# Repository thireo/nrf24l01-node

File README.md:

Indoor climate measuring nodes running on a single coin cell battery. Measurements done every 5 minutes (not necessarily sent at same interval).

Specs. for now:

* NRF24L01 - 2.4GHz module
* SAMD21G18 - MCU
* CR2450 - Coin cell battery ~ 500+mAh
* BME280 - Temperature, Humidity & Pressure.
* DS1302 - Ultra low power RTC for waking up node / Perhaps instead TLP5010.

Ideas to improve battery life:
Latch/flippydifloppy to control power to MCU + SIP32431.

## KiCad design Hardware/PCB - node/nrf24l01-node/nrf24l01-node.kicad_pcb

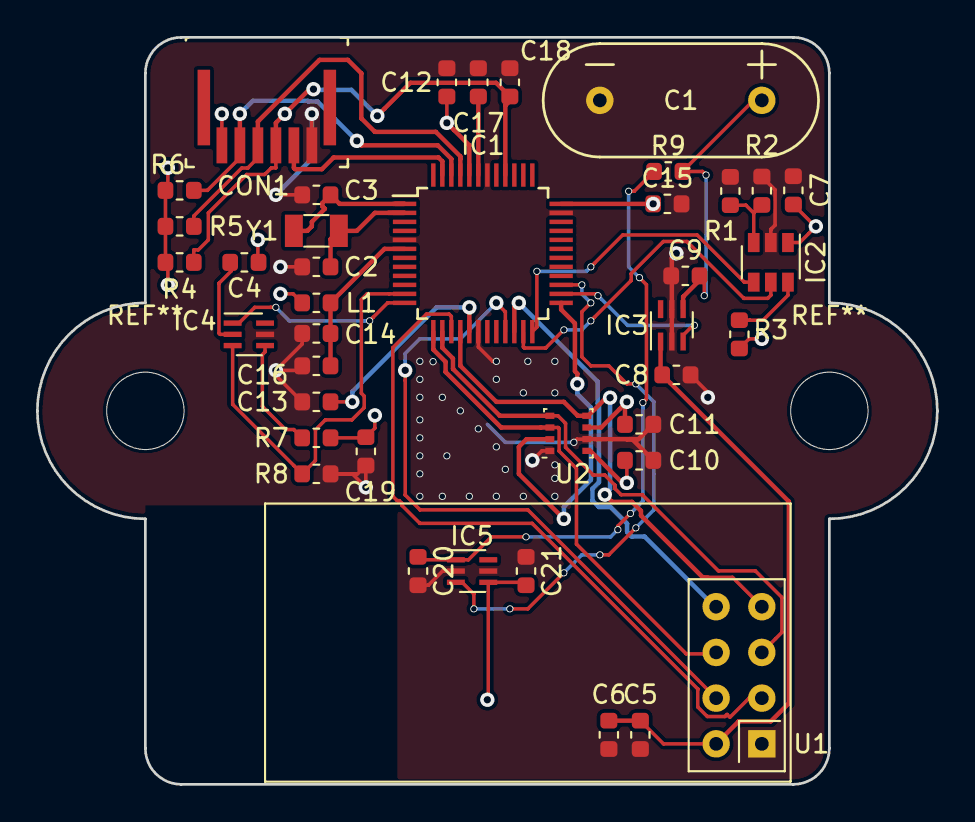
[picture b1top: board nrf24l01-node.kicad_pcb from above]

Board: 2 copper layers, 50.0 x 41.5 mm, 41 parts (1 on the bottom side), 30 nets.

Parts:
BT1: Coin Cell; BatteryHolder_Keystone_3008_1x2450
C1: SuperCap; SCMQ14C474PRBA0
C2, C3: 15pF; C_0603_1608Metric
C4, C6, C7, C8, C9, C10, C11, C13, C15, C16, C17, C18, C19, C20, C21: 100nF; C_0603_1608Metric
C5: 100uF; C_0603_1608Metric
C12, C14: 10uF; C_0603_1608Metric
CON1: FPC_6POS; HFW6R_2STE1LF
IC1: ATSAMD21G18A-AU; TQFP-48_7x7mm_P0.5mm
IC2: TLP5010; SOT-23-6
IC3, IC4, IC5: SIP32431; SC-70-6
L1: SMD-FERRITE-CHIP-120-OHM-500MA_0603_; C_0603_1608Metric
R1: 54.9k; R_0603_1608Metric
R2: 196k; R_0603_1608Metric
R3, R4, R5, R6, R7: 100k; R_0603_1608Metric
R8: 1M; R_0603_1608Metric
R9: CAP_CHARGE_R; R_0603_1608Metric
U1: NRF24L01_Breakout; nRF24L01_Breakout
U2: BME280; Bosch_LGA-8_2.5x2.5mm_P0.65mm_ClockwisePinNumbering
Y1: Crystal_Small; Crystal_SMD_3215-2Pin_3.2x1.5mm

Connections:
/BME280_SCK: IC1.14, U1.5, U2.4
/BME280_SDI: IC1.13, U1.6, U2.3
/BME280_SDO: IC1.16, U1.7, U2.5
/BME280_SS: IC1.25, U2.2
/MCU_RESET: C18.2, CON1.4, IC1.40, R4.2
/NRF_CE: IC1.15, U1.3
/NRF_CS: IC1.21, U1.4
/NRF_IRQ: IC1.22, U1.8
/NRF_VCC_EN: IC1.26, IC3.3
/NRF_VCC_IN: C1.1, C9.2, IC3.4, R9.2
/NRF_VCC_OUT: C5.1, C6.1, C8.1, IC3.1, U1.2
/RESET_BTN: IC2.3, R1.1, R2.1
/SIG_DONE: IC1.24, IC2.4
/SIG_WAKE: IC1.23, IC2.5
/SUPER_CAP_EN: IC1.27, IC5.3
/SWCLK: CON1.3, IC1.45, R5.2
/SWDIO: CON1.2, IC1.46, R6.2
/UART_TX: CON1.5, IC1.47
/VBAT_ADC: IC1.12, IC4.1
/VBAT_ADC_EN: IC1.11, IC4.3, R8.2
/VDDANA: C14.1, C16.1, IC1.6, L1.2
/VDDCORE: C17.1, IC1.43
GND: BT1.2, C1.2, C2.2, C3.2, C5.2, C6.2, C7.2, C8.2, C9.1, C10.2, C11.2, C12.2, C13.2, C14.2, C15.2, C16.2, C17.2, C18.1, C19.2, C20.2, C21.1, CON1.6, IC1.5, IC1.18, IC1.35, IC1.42, IC2.2, IC3.2, IC3.5, IC4.5, IC5.2, IC5.5, R1.2, R2.2, R8.1, U1.1, U2.1, U2.7
unnamed: C2.1, IC1.2, Y1.2
unnamed: C3.1, IC1.1, Y1.1
unnamed: C4.2, IC4.2
unnamed: C20.1, IC5.1, R9.1
unnamed: IC2.6, R3.2
unnamed: IC4.4, R7.2
VCC: BT1.1, C4.1, C7.1, C10.1, C11.1, C12.1, C13.1, C15.1, C19.1, C21.2, CON1.1, IC1.17, IC1.36, IC1.44, IC2.1, IC5.4, L1.1, R3.1, R4.1, R5.1, R6.1, R7.1, U2.6, U2.8

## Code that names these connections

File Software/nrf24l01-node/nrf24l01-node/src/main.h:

/*
 * main.h
 *
 * Created: 19-12-2017 17:46:26
 *  Author: Andreas
 */ 


#ifndef MAIN_H_
#define MAIN_H_

#include "asf.h"

#define SYSTEM_CLK 8000000


// defines for SAMD21
#define PORTGROUP_A		0
#define PORTGROUP_B		1

#define GPIO_SERCOM_ALT_D 3 //peripheral function D - SERCOM-ALT

#define GCM_SERCOM0_CORE          (0x14U)
#define GCM_SERCOM1_CORE          (0x15U)
#define GCM_SERCOM2_CORE          (0x16U)
#define GCM_SERCOM3_CORE          (0x17U)
#define GCM_SERCOM4_CORE          (0x18U)
#define GCM_SERCOM5_CORE          (0x19U)

#define SAMPLE_RATE_x16 0


#define SOFTWARE_VERSION 42


#define NRF_VCC_EN PIN_PA17
#define SIG_WAKE PIN_PA14
#define SIG_WAKE_MUX PINMUX_PA14A_EIC_EXTINT14
#define SIG_DONE_PIN PIN_PA15
#define SIG_DONE_MUX PINMUX_PA15A_EIC_EXTINT15
#define VBAT_ADC_PIN PIN_PA07
#define VBAT_ADC_PORT PORT_PA07
#define VBAT_ADC_EN_PIN PIN_PA06
#define VBAT_ADC_EN_PORT PORT_PA06

bool woke;

#endif /* MAIN_H_ */

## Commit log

2018-11-30 Current consumptions
    Added current consumption calculation sheet.
2018-12-03 README.md edited online with Bitbucket
2018-12-03 Updated spreadsheet
    Current Consumption Excel file updated
2018-12-07 Did some Excel stuff
    Updated Excel sheet of current consumptions with more real values.
    Added "real" NRF24L01 times.
    Plan is to power off NRF24L01 in SLEEP period.
2018-12-07 Initial PCB commit
2018-12-10 temp commit
2018-12-17 First Software commit
    Initial SW commit. Functioning BME280 n stuff.
2018-12-17 BME280 clean up
    Did some structuring on the BME280 library.
    Data is now passed to bme280_data structure.
2019-01-17 Initial Hardware commit
2019-01-17 Working software copy
2019-01-17 Updated current consumption
    dunno changes specifically..
2019-04-15 Initial board bring SW - HW Rev. 2
    Functioning:
    BME280
    TPL5010
    UART
2020-08-21 Sorry future me
